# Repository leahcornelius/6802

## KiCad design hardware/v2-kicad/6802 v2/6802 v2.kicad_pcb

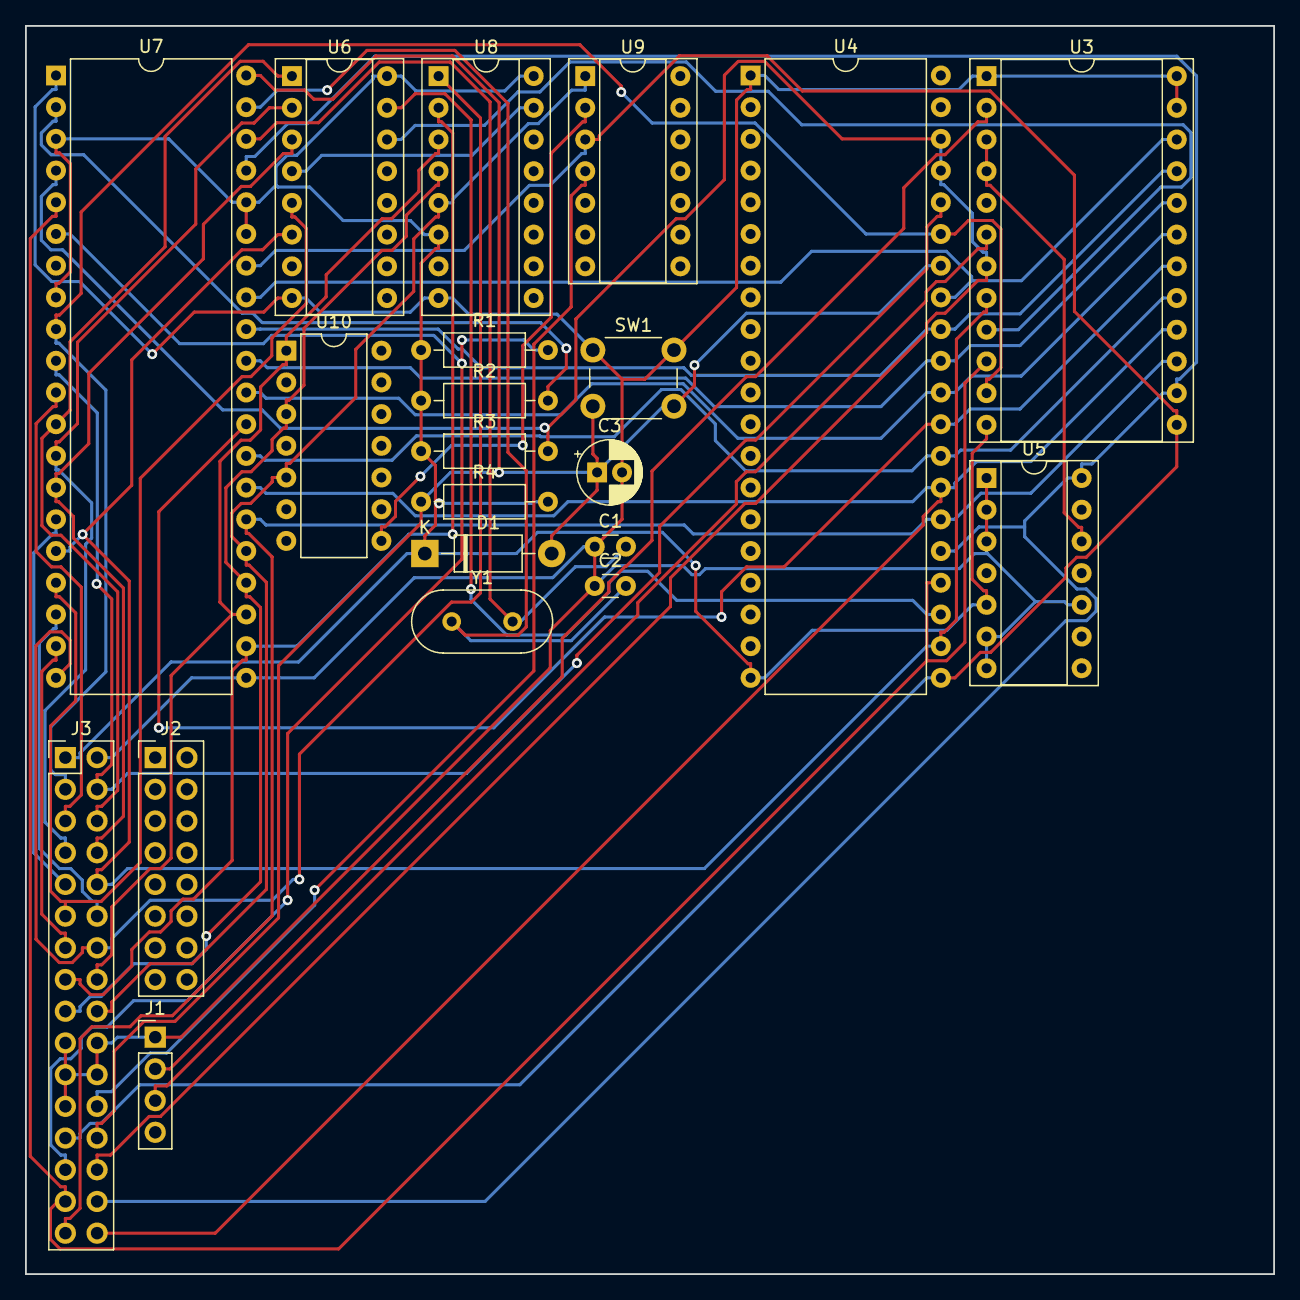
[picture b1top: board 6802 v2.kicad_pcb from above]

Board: 2 copper layers, 100.0 x 100.0 mm, 21 parts (0 on the bottom side), 43 nets.

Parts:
C1, C2: 27pF; C_Disc_D3.0mm_W1.6mm_P2.50mm
C3: 10uF; CP_Radial_D5.0mm_P2.00mm
D1: 1N5819; D_DO-41_SOD81_P10.16mm_Horizontal
J1: UART connector; PinHeader_1x04_P2.54mm_Vertical
J2: Conn_02x08_Row_Letter_First; PinHeader_2x08_P2.54mm_Vertical
J3: Conn_02x16_Counter_Clockwise; PinHeader_2x16_P2.54mm_Vertical
R1, R2, R3, R4: 3.3k; R_Axial_DIN0207_L6.3mm_D2.5mm_P10.16mm_Horizontal
SW1: Reset; SW_PUSH_6mm
U3: MC68B50; DIP-24_W15.24mm_Socket
U4: 6821; DIP-40_W15.24mm
U5: 74LS90; DIP-14_W7.62mm_Socket
U6, U8: 74LS138; DIP-16_W7.62mm_Socket
U7: MC6802; DIP-40_W15.24mm
U9: 74LS04; DIP-14_W7.62mm_Socket
U10: 74HC04; DIP-14_W7.62mm
Y1: 4MHz Crystal; Crystal_HC49-U_Vertical

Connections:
+5V: D1.1 (K), J3.1, R1.1, R2.1, R3.1, R4.2, U3.12 (VCC), U4.20 (VCC), U5.5 (VCC), U6.16 (VCC), U7.3 (MR), U7.8 (VCC), U7.35 (VCC_STANDBY), U7.36 (RE), U8.6 (E3), U8.16 (VCC)
A0: J3.3, U3.11 (RS), U4.35 (RS1), U7.9 (A0)
A1: J3.4, U4.36 (RS0), U7.10 (A1)
A2: J3.5, U7.11 (A2)
A3: J3.6, U6.1 (A0), U7.12 (A3)
A4: J3.7, U6.2 (A1), U7.13 (A4)
A5: J3.8, U6.3 (A2), U7.14 (A5)
A6: J3.9, U7.15 (A6)
A7: J3.10, U3.8 (CS0), U4.22 (CS0), U6.6 (E3), U7.16 (A7)
A8: J3.11, U6.5 (E2), U7.17 (A8)
A9: J3.12, U7.18 (A9)
A10: J3.13, U7.19 (A10)
A11: J3.14, U7.20 (A11), U8.1 (A0)
A12: J3.15, U7.22 (A12), U8.2 (A1)
A13: J3.16, U7.23 (A13), U8.3 (A2), U10.1
A14: J3.17, U7.24 (A14), U8.4 (E1), U10.3
A15: J3.18, U7.25 (A15), U8.5 (E2), U9.1, U10.5
CLK_{UART0}: U3.3 (Rx_CLK), U3.4 (Tx_CLK), U5.12 (Q0)
D0: U3.22 (D0), U4.33 (D0), U7.33 (D0)
D1: U3.21 (D1), U4.32 (D1), U7.32 (D1)
D2: U3.20 (D2), U4.31 (D2), U7.31 (D2)
D3: U3.19 (D3), U4.30 (D3), U7.30 (D3)
D4: U3.18 (D4), U4.29 (D4), U7.29 (D4)
D5: U3.17 (D5), U4.28 (D5), U7.28 (D5)
D6: J3.32, U3.16 (D6), U4.27 (D6), U7.27 (D6)
D7: J3.31, U3.15 (D7), U4.26 (D7), U7.26 (D7)
E: J3.30, U3.14 (E), U4.25 (ENABLE), U5.14 (CP0), U7.37 (E)
GND: C1.1, C2.1, C3.2, J1.1, J3.2, J3.19, J3.20, J3.21, J3.22, J3.23, SW1.1, U3.1 (VSS), U3.23 (~DCD), U3.24 (~CTS), U4.1 (VSS), U5.1 (CP1..3), U5.2 (R0(1)), U5.3 (R0(2)), U5.6 (R9(1)), U5.7 (R9(2)), U5.10 (GND), U6.8 (GND), U7.1 (VSS), U7.21 (VSS), U8.8 (GND)
unnamed: C2.2, U7.39 (EXTAL), Y1.1
unnamed: C1.2, U7.38 (XTAL), Y1.2
RX: J1.2, U3.2 (Rx_Data)
R/~W: J3.25, U3.13 (R/~W), U4.21 (R/~W), U7.34 (R/~W), U9.3
TX: J1.3, U3.6 (Tx_Data)
VMA: J3.29, U3.10 (CS1), U4.24 (CS1), U7.5 (VMA)
~CS^{13_{H}}: U6.4 (E1), U8.15 (O0)
~CS_{PIA}: U4.23 (~CS2), U6.15 (O0)
~CS_{ROM}: U9.2, U10.8
~CS_{UART0}: U3.9 (~CS2), U6.14 (O1)
~HALT: R2.2, U7.2 (~HALT)
~IRQ: J3.28, R3.2, U3.7 (~IRQ), U4.37 (~IRQB), U4.38 (~IRQA), U7.4 (~IRQ)
~NMI: J3.27, R1.2, U7.6 (~NMI)
~RESET: C3.1, D1.2 (A), J3.26, R4.1, SW1.2, U4.34 (~RESET), U7.40 (~RESET)
~R: J3.24, U9.4

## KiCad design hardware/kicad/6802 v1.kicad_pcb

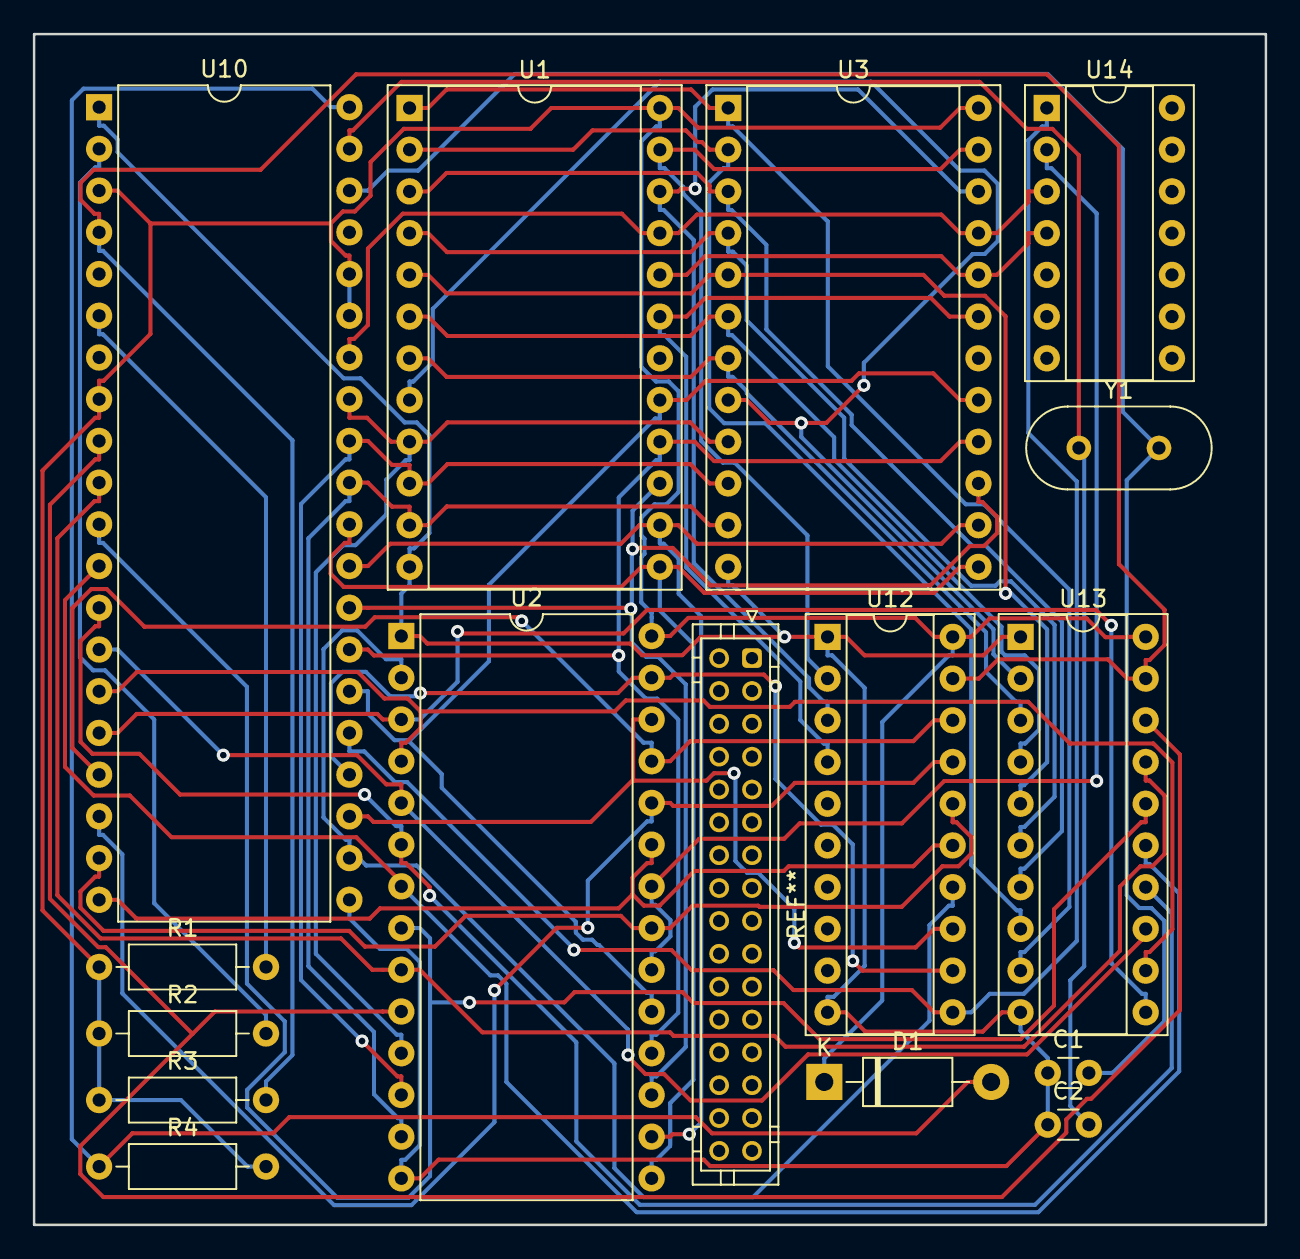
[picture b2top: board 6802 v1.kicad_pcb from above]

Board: 2 copper layers, 75.0 x 72.5 mm, 15 parts (0 on the bottom side), 46 nets.

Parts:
C1, C2: 27pF; C_Disc_D3.0mm_W1.6mm_P2.50mm
D1: 1N5819; D_DO-41_SOD81_P10.16mm_Horizontal
R1, R2, R3, R4: 3.3k; R_Axial_DIN0207_L6.3mm_D2.5mm_P10.16mm_Horizontal
U1, U3: UM6116; DIP-24_W15.24mm_Socket
U2: 27C512; DIP-28_W15.24mm
U10: MC6802; DIP-40_W15.24mm
U12, U13: 74LS245; DIP-20_W7.62mm_Socket
U14: 74LS04; DIP-14_W7.62mm_Socket
Y1: 4MHz Crystal; Crystal_HC49-U_Vertical

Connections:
+5V: D1.1 (K), R1.1, R2.1, R3.1, R4.2, U1.24 (VCC), U2.28 (VCC), U3.24 (VCC), U10.3 (MR), U10.8 (VCC), U10.35 (VCC_STANDBY), U10.36 (RE), U12.20 (VCC), U13.20 (VCC)
A0: U2.10 (A0), U10.9 (A0), U13.18 (B0)
A1: U2.9 (A1), U10.10 (A1), U13.17 (B1)
A2: U2.8 (A2), U10.11 (A2), U13.16 (B2)
A3: U2.7 (A3), U10.12 (A3), U13.15 (B3)
A4: U2.6 (A4), U10.13 (A4), U13.14 (B4)
A5: U2.5 (A5), U10.14 (A5), U13.13 (B5)
A6: U2.4 (A6), U10.15 (A6), U13.12 (B6)
A7: U2.3 (A7), U10.16 (A7), U13.11 (B7)
A8: U2.25 (A8), U10.17 (A8), U12.18 (B0)
A9: U2.24 (A9), U10.18 (A9), U12.17 (B1)
A10: U2.21 (A10), U10.19 (A10), U12.16 (B2)
A11: U2.23 (A11), U10.20 (A11), U12.15 (B3)
A12: U2.2 (A12), U10.22 (A12), U12.14 (B4)
A13: U2.26 (A13), U10.23 (A13), U12.13 (B5)
A14: U2.27 (A14), U10.24 (A14), U12.12 (B6)
A15: U10.25 (A15), U12.11 (B7), U14.1
A_{b}0: U1.8 (A0), U3.8 (A0), U13.2 (A0)
A_{b}1: U1.7 (A1), U3.7 (A1), U13.3 (A1)
A_{b}2: U1.6 (A2), U3.6 (A2), U13.4 (A2)
A_{b}3: U1.5 (A3), U3.5 (A3), U13.5 (A3)
A_{b}4: U1.4 (A4), U3.4 (A4), U13.6 (A4)
A_{b}5: U1.3 (A5), U3.3 (A5), U13.7 (A5)
A_{b}6: U1.2 (A6), U3.2 (A6), U13.8 (A6)
A_{b}7: U1.1 (A7), U3.1 (A7), U13.9 (A7)
A_{b}8: U1.23 (A8), U3.23 (A8), U12.2 (A0)
A_{b}9: U1.22 (A9), U3.22 (A9), U12.3 (A1)
A_{b}10: U1.19 (A10), U3.19 (A10), U12.4 (A2)
D0: U1.9 (Q1), U2.11 (D0), U3.9 (Q1), U10.33 (D0)
D1: U1.10 (Q2), U2.12 (D1), U3.10 (Q2), U10.32 (D1)
D2: U1.11 (Q3), U2.13 (D2), U3.11 (Q3), U10.31 (D2)
D3: U1.13 (Q4), U2.15 (D3), U3.13 (Q4), U10.30 (D3)
D4: U1.14 (Q5), U2.16 (D4), U3.14 (Q5), U10.29 (D4)
D5: U1.15 (Q6), U2.17 (D5), U3.15 (Q6), U10.28 (D5)
D6: U1.16 (Q7), U2.18 (D6), U3.16 (Q7), U10.27 (D6)
D7: U1.17 (Q8), U2.19 (D7), U3.17 (Q8), U10.26 (D7)
DMA: R3.2, U10.4 (~IRQ), U12.19 (CE), U13.19 (CE)
GND: C1.1, C2.1, U1.12 (GND), U2.1 (A15), U2.14 (GND), U3.12 (GND), U10.1 (VSS), U10.21 (VSS), U12.1 (A->B), U12.10 (GND), U13.1 (A->B), U13.10 (GND)
unnamed: C2.2, U10.39 (EXTAL), Y1.1
unnamed: C1.2, U10.38 (XTAL), Y1.2
R/~W: U1.21 (~WE), U3.21 (~WE), U10.34 (R/~W), U14.3
~CS_{ROM}: U2.20 (~CE), U2.22 (~OE), U14.2
~IRQ: R2.2, U10.2 (~HALT)
~NMI: R1.2, U10.6 (~NMI)
~RESET: D1.2 (A), R4.1, U10.40 (~RESET)
~R: U1.20 (~OE), U3.20 (~OE), U14.4

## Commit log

2023-05-16 Create assembly program template
2023-05-16 add uart
2023-05-16 fix kicad
2023-05-16 Kicad works again maybe?
2023-05-18 18may
2023-05-19 Change filename
2023-05-19 Update gitnore
2023-05-23 Cont
2023-05-24 Start more complex demo
2023-05-27 Uart working
2023-05-27 Bug fixes on bitspitter test asm
2023-05-27 Add some DSK imgs relating to 6800 FLEX OS
2023-05-27 Start PCB design
2023-05-27 Ensure IRQ processed by handler
2023-05-27 Ensure TX rdy interupts enabled from ACIA
2023-05-27 Fix branch conditions
2023-05-27 Disable tx ready interupts when no pending bytes (hacky fix?)
2023-05-27 Dont disable tx INTERUPTS unless speced
2023-05-29 Improve UART test code and add comments
2023-05-29 Use acc B, move PIA output to IRQ handler
2023-06-05 Lots of changes
2023-06-06 Fix echo bug
2023-06-07 Amen, MKBUG
2023-06-08 cONT UPDATES
